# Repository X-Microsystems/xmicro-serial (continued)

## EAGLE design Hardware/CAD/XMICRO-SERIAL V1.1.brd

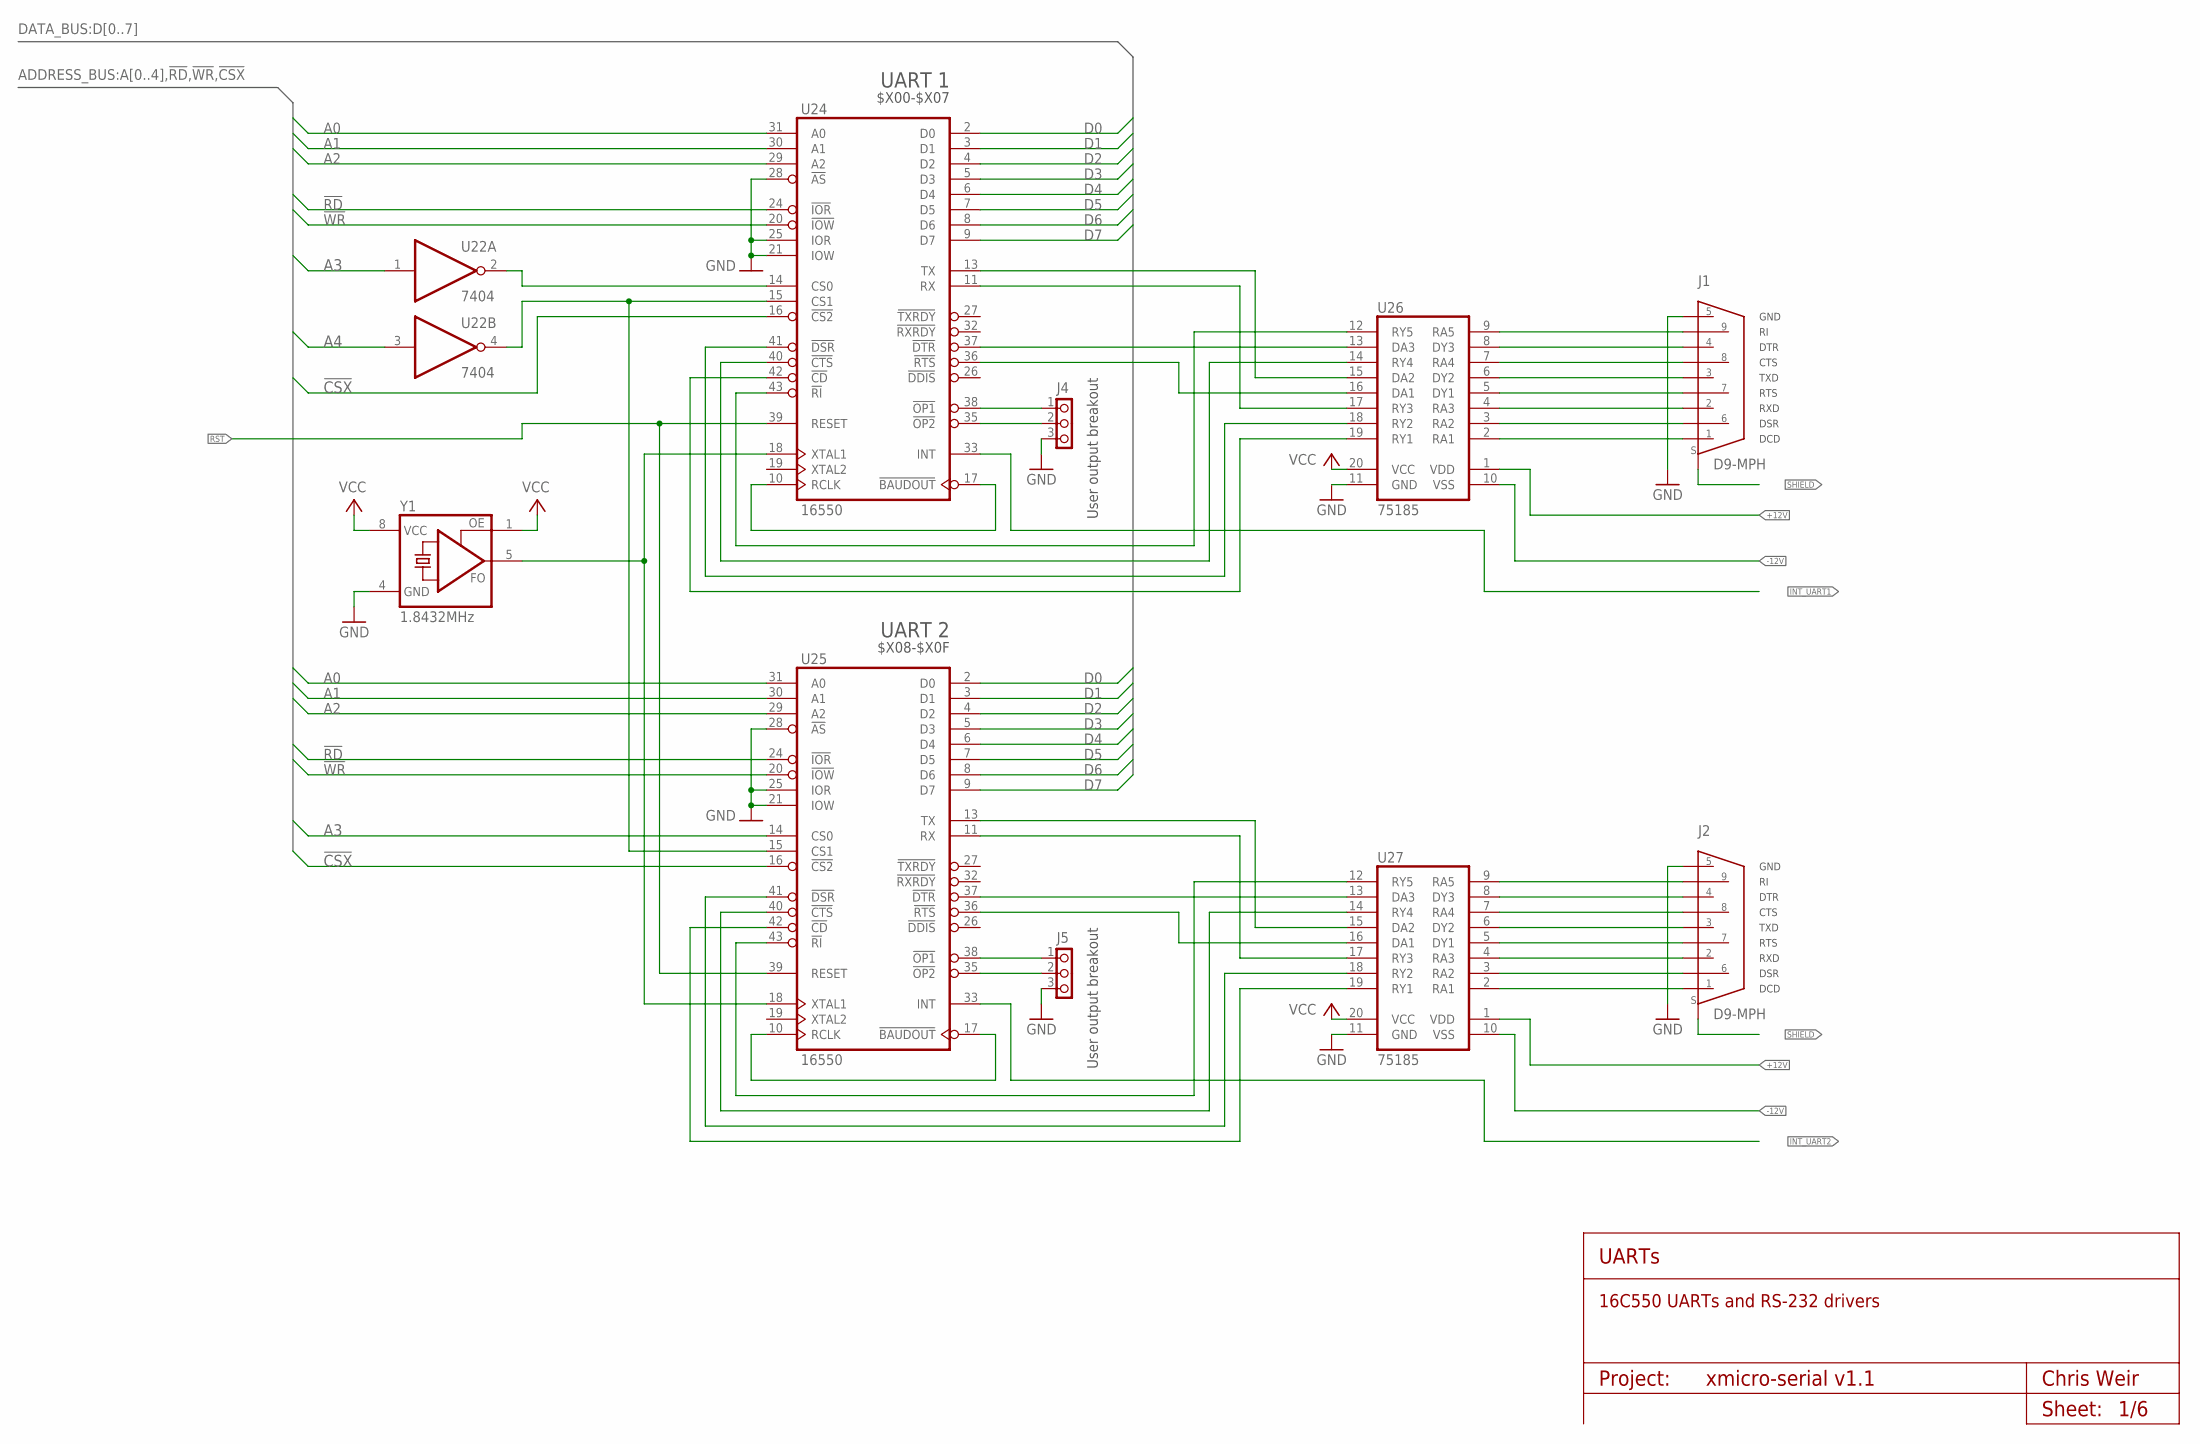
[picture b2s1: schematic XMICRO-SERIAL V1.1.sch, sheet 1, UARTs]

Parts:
J1, J2: D9-MPH; D9-H
J4, J5: PINHD1X3; 1X03
U22: 7404; DIL14
U24, U25: 16550; S44
U26, U27: 75185; DIL20
Y1: 1.8432MHz; DIL08S

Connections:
!CSX: U24.16 (!CS2), U25.16 (!CS2); also elsewhere on the board
!RD: U24.24 (!IOR), U25.24 (!IOR); also elsewhere on the board
!WR: U24.20 (!IOW), U25.20 (!IOW); also elsewhere on the board
+12V: U26.1 (VDD), U27.1 (VDD); also elsewhere on the board
-12V: U26.10 (VSS), U27.10 (VSS); also elsewhere on the board
A0: U24.31 (A0), U25.31 (A0); also elsewhere on the board
A1: U24.30 (A1), U25.30 (A1); also elsewhere on the board
A2: U24.29 (A2), U25.29 (A2); also elsewhere on the board
A3: U22.1 (I), U25.14 (CS0); also elsewhere on the board
A4: U22.3 (I); also elsewhere on the board
D0: U24.2 (D0), U25.2 (D0); also elsewhere on the board
D1: U24.3 (D1), U25.3 (D1); also elsewhere on the board
D2: U24.4 (D2), U25.4 (D2); also elsewhere on the board
D3: U24.5 (D3), U25.5 (D3); also elsewhere on the board
D4: U24.6 (D4), U25.6 (D4); also elsewhere on the board
D5: U24.7 (D5), U25.7 (D5); also elsewhere on the board
D6: U24.8 (D6), U25.8 (D6); also elsewhere on the board
D7: U24.9 (D7), U25.9 (D7); also elsewhere on the board
GND: J1.P$5, J2.P$5, J4.3, J5.3, U22.7 (GND), U24.21 (IOW), U24.22 (GND), U24.25 (IOR), U24.28 (!AS), U25.21 (IOW), U25.22 (GND), U25.25 (IOR), U25.28 (!AS), U26.11 (GND), U27.11 (GND), Y1.4 (GND); also elsewhere on the board
INT_UART1: U24.33 (INT); also elsewhere on the board
INT_UART2: U25.33 (INT); also elsewhere on the board
unnamed: J1.P$1, U26.2 (RA1)
unnamed: J1.P$2, U26.4 (RA3)
unnamed: J1.P$3, U26.6 (DY2)
unnamed: J1.P$4, U26.8 (DY3)
unnamed: J1.P$6, U26.3 (RA2)
unnamed: J1.P$7, U26.5 (DY1)
unnamed: J1.P$8, U26.7 (RA4)
unnamed: J1.P$9, U26.9 (RA5)
unnamed: J2.P$1, U27.2 (RA1)
unnamed: U24.43 (!RI), U26.12 (RY5)
unnamed: U24.37 (!DTR), U26.13 (DA3)
unnamed: U24.40 (!CTS), U26.14 (RY4)
unnamed: U24.13 (TX), U26.15 (DA2)
unnamed: U24.36 (!RTS), U26.16 (DA1)
unnamed: U24.11 (RX), U26.17 (RY3)
unnamed: U24.41 (!DSR), U26.18 (RY2)
unnamed: U24.42 (!CD), U26.19 (RY1)
unnamed: U24.10 (RCLK), U24.17 (!BAUDOUT)
unnamed: J2.P$2, U27.4 (RA3)
unnamed: J2.P$3, U27.6 (DY2)
unnamed: J2.P$4, U27.8 (DY3)
unnamed: J2.P$6, U27.3 (RA2)
unnamed: J2.P$7, U27.5 (DY1)
unnamed: J2.P$8, U27.7 (RA4)
unnamed: J2.P$9, U27.9 (RA5)
unnamed: U25.43 (!RI), U27.12 (RY5)
unnamed: U25.37 (!DTR), U27.13 (DA3)
unnamed: U25.40 (!CTS), U27.14 (RY4)
unnamed: U25.13 (TX), U27.15 (DA2)
unnamed: U25.36 (!RTS), U27.16 (DA1)
unnamed: U25.11 (RX), U27.17 (RY3)
unnamed: U25.41 (!DSR), U27.18 (RY2)
unnamed: U25.42 (!CD), U27.19 (RY1)
unnamed: U25.10 (RCLK), U25.17 (!BAUDOUT)
unnamed: U22.2 (O), U24.14 (CS0)
unnamed: U22.4 (O), U24.15 (CS1), U25.15 (CS1)
unnamed: U24.18 (XTAL1), U25.18 (XTAL1), Y1.5 (FO)
unnamed: J5.1, U25.38 (!OP1)
unnamed: J5.2, U25.35 (!OP2)
unnamed: J4.1, U24.38 (!OP1)
unnamed: J4.2, U24.35 (!OP2)
RST: U24.39 (RESET), U25.39 (RESET); also elsewhere on the board
SHIELD: J1.S1, J1.S2, J2.S1, J2.S2; also elsewhere on the board
VCC: U22.14 (VCC), U24.44 (VCC), U25.44 (VCC), U26.20 (VCC), U27.20 (VCC), Y1.1 (OE), Y1.8 (VCC); also elsewhere on the board

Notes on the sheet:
DTR
CTS
TXD
RTS
RXD
DSR
DCD
User output breakout
GND
Project:
UARTs
Chris Weir
Sheet:
16C550 UARTs and RS-232 drivers
UART 1
$X00-$X07
UART 2
$X08-$X0F

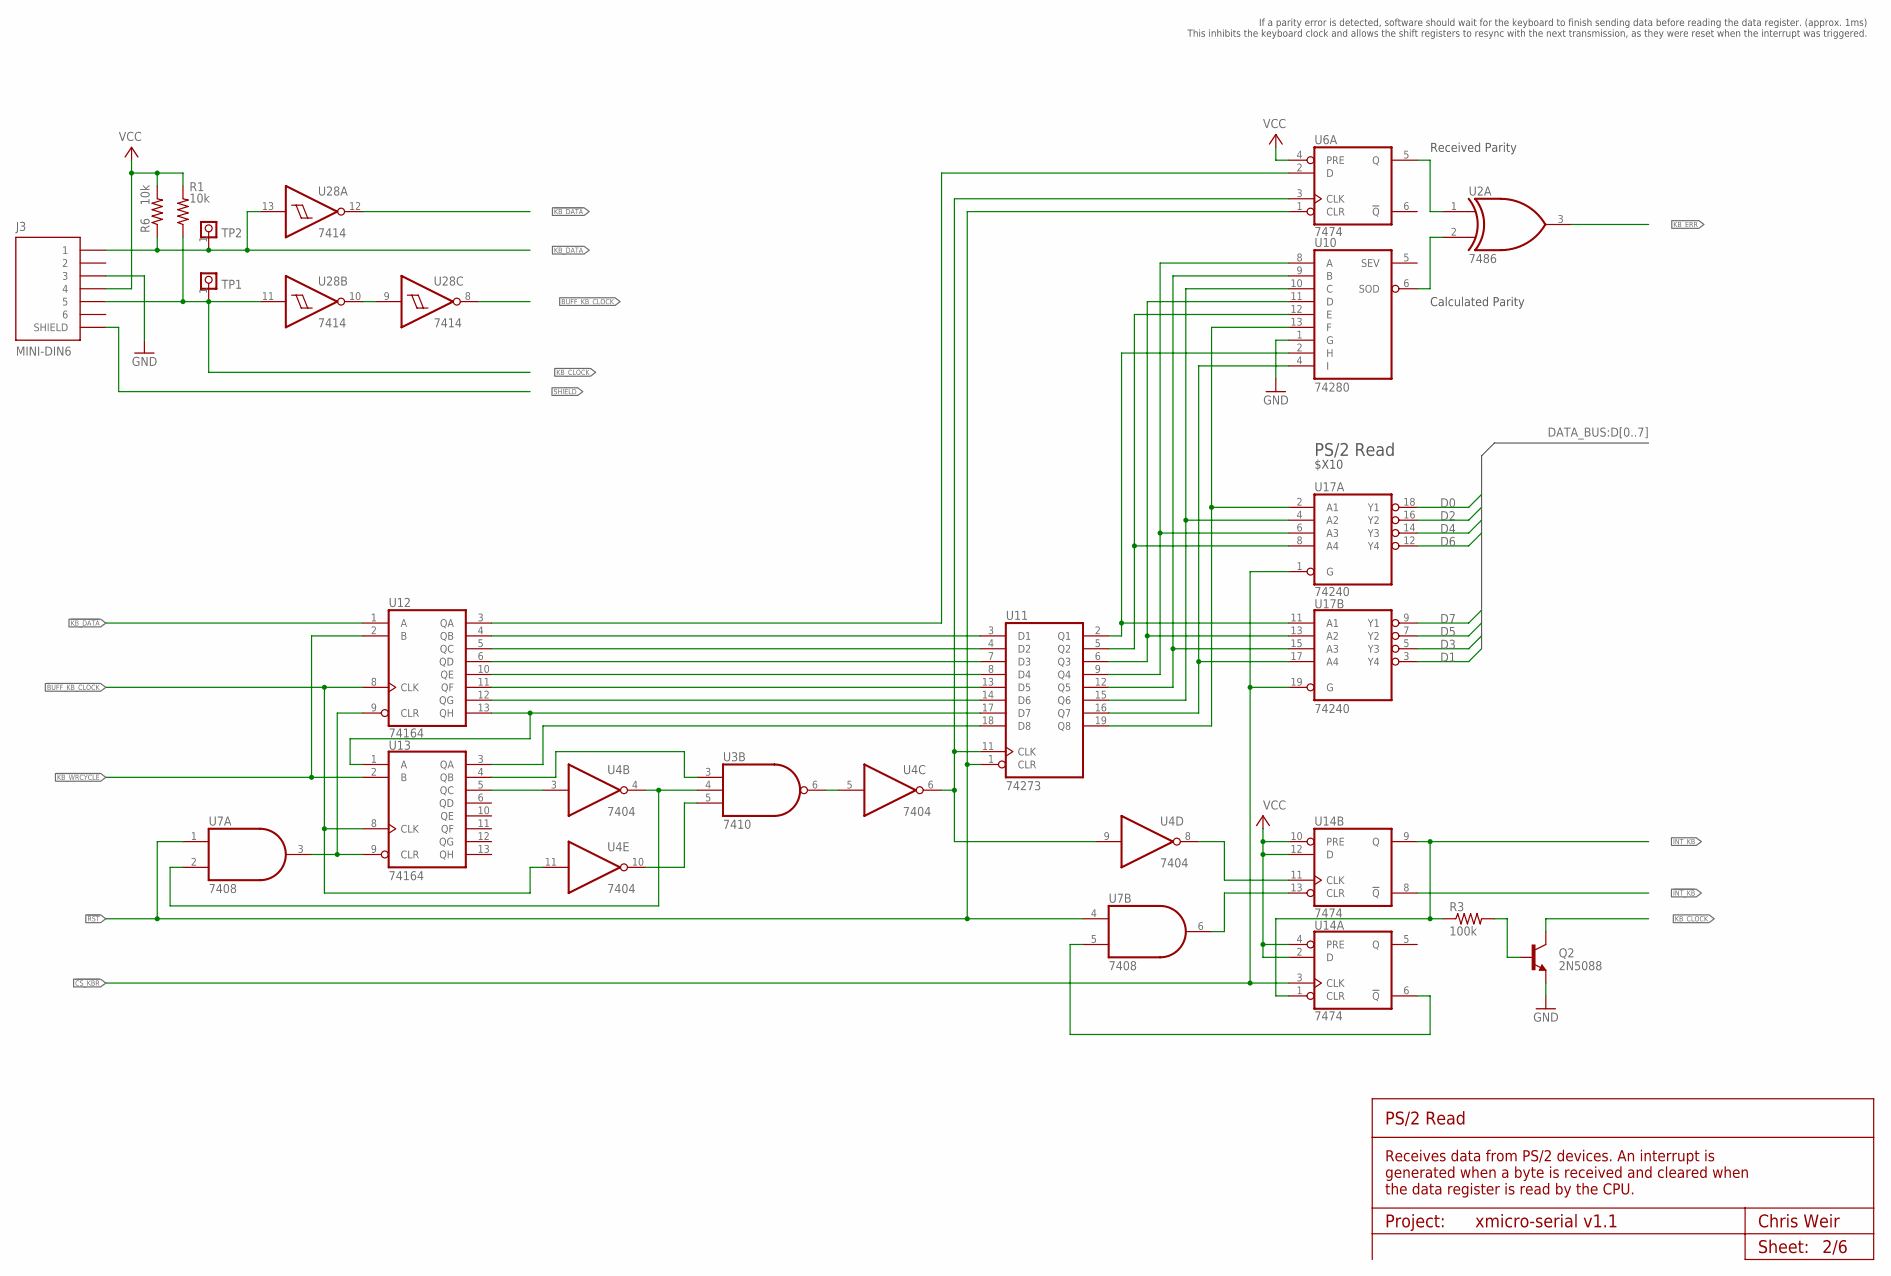
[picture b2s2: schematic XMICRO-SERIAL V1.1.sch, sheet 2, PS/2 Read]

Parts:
J3: MINI-DIN6
Q2: 2N5088; TO92
R1, R6: 10k; 0207/10
R3: 100k; 0207/10
TP1, TP2: PINHD-1X1; 1X01
U2: 7486; DIL14
U3: 7410; DIL14
U4: 7404; DIL14
U6, U14: 7474; DIL14
U7: 7408; DIL14
U10: 74280; DIL14
U11: 74273; DIL20
U12, U13: 74164; DIL14
U17: 74240; DIL20
U28: 7414; DIL14

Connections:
!CS_KBR: U14.3 (CLK), U17.1 (G), U17.19 (G); also elsewhere on the board
!INT_KB: U14.8 (!Q); also elsewhere on the board
!KB_DATA: U12.1 (A), U28.12 (O); also elsewhere on the board
!KB_WRCYCLE: U12.2 (B), U13.2 (B); also elsewhere on the board
!RST: U6.1 (CLR), U7.1 (I0), U7.4 (I0), U11.1 (CLR); also elsewhere on the board
BUFF_KB_CLOCK: U4.11 (I), U12.8 (CLK), U13.8 (CLK), U28.8 (O); also elsewhere on the board
D0: U17.18 (Y1); also elsewhere on the board
D1: U17.3 (Y4); also elsewhere on the board
D2: U17.16 (Y2); also elsewhere on the board
D3: U17.5 (Y3); also elsewhere on the board
D4: U17.14 (Y3); also elsewhere on the board
D5: U17.7 (Y2); also elsewhere on the board
D6: U17.12 (Y4); also elsewhere on the board
D7: U17.9 (Y1); also elsewhere on the board
GND: J3.3, Q2.1 (E), U2.7 (GND), U3.7 (GND), U4.7 (GND), U6.7 (GND), U7.7 (GND), U10.1 (G), U10.7 (GND), U11.10 (GND), U12.7 (GND), U13.7 (GND), U14.7 (GND), U17.10 (GND), U28.7 (GND); also elsewhere on the board
INT_KB: R3.1, U14.1 (CLR), U14.9 (Q); also elsewhere on the board
KB_CLOCK: J3.5, Q2.3 (C), R1.1, TP1.1, U28.11 (I); also elsewhere on the board
KB_DATA: J3.1, R6.1, TP2.1, U28.13 (I); also elsewhere on the board
KB_ERR: U2.3 (O); also elsewhere on the board
unnamed: U3.6 (O), U4.5 (I)
unnamed: U4.8 (O), U14.11 (CLK)
unnamed: U28.9 (I), U28.10 (O)
unnamed: U11.17 (D7), U12.13 (QH), U13.1 (A)
unnamed: U11.18 (D8), U13.3 (QA)
unnamed: U4.3 (I), U13.5 (QC)
unnamed: U3.4 (I1), U4.4 (O), U7.2 (I1)
unnamed: U4.6 (O), U4.9 (I), U6.3 (CLK), U11.11 (CLK)
unnamed: U3.3 (I0), U13.4 (QB)
unnamed: U11.14 (D6), U12.12 (QG)
unnamed: U11.13 (D5), U12.11 (QF)
unnamed: U11.7 (D3), U12.6 (QD)
unnamed: U11.4 (D2), U12.5 (QC)
unnamed: U11.3 (D1), U12.4 (QB)
unnamed: U6.2 (D), U12.3 (QA)
unnamed: U7.3 (O), U12.9 (CLR), U13.9 (CLR)
unnamed: U7.6 (O), U14.13 (CLR)
unnamed: U2.1 (I0), U6.5 (Q)
unnamed: U10.13 (F), U11.19 (Q8), U17.2 (A1)
unnamed: U10.4 (I), U11.16 (Q7), U17.17 (A4)
unnamed: U10.10 (C), U11.15 (Q6), U17.4 (A2)
unnamed: U10.9 (B), U11.12 (Q5), U17.15 (A3)
unnamed: U10.11 (D), U11.6 (Q3), U17.13 (A2)
unnamed: U10.12 (E), U11.5 (Q2), U17.8 (A4)
unnamed: U10.2 (H), U11.2 (Q1), U17.11 (A1)
unnamed: U10.8 (A), U11.9 (Q4), U17.6 (A3)
unnamed: U2.2 (I1), U10.6 (SOD)
unnamed: U3.5 (I2), U4.10 (O)
unnamed: Q2.2 (B), R3.2
unnamed: U7.5 (I1), U14.6 (!Q)
SHIELD: J3.G$1 (SHIELD), J3.G$2 (SHIELD), J3.G$3 (SHIELD); also elsewhere on the board
UC4: U11.8 (D4), U12.10 (QE)
VCC: J3.4, R1.2, R6.2, U2.14 (VCC), U3.14 (VCC), U4.14 (VCC), U6.4 (PRE), U6.14 (VCC), U7.14 (VCC), U10.14 (VCC), U11.20 (VCC), U12.14 (VCC), U13.14 (VCC), U14.2 (D), U14.4 (PRE), U14.10 (PRE), U14.12 (D), U14.14 (VCC), U17.20 (VCC), U28.14 (VCC); also elsewhere on the board

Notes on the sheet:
Received Parity
Calculated Parity
If a parity error is detected, software should wait for the keyboard to finish sending data before reading the data register. (approx. 1ms) This inhibits the keyboard clock and allows the shift registers to resync with the next transmission, as they were reset when the interrupt was triggered.
Project:
PS/2 Read
Chris Weir
Sheet:
Receives data from PS/2 devices. An interrupt is generated when a byte is received and cleared when the data register is read by the CPU.
$X10

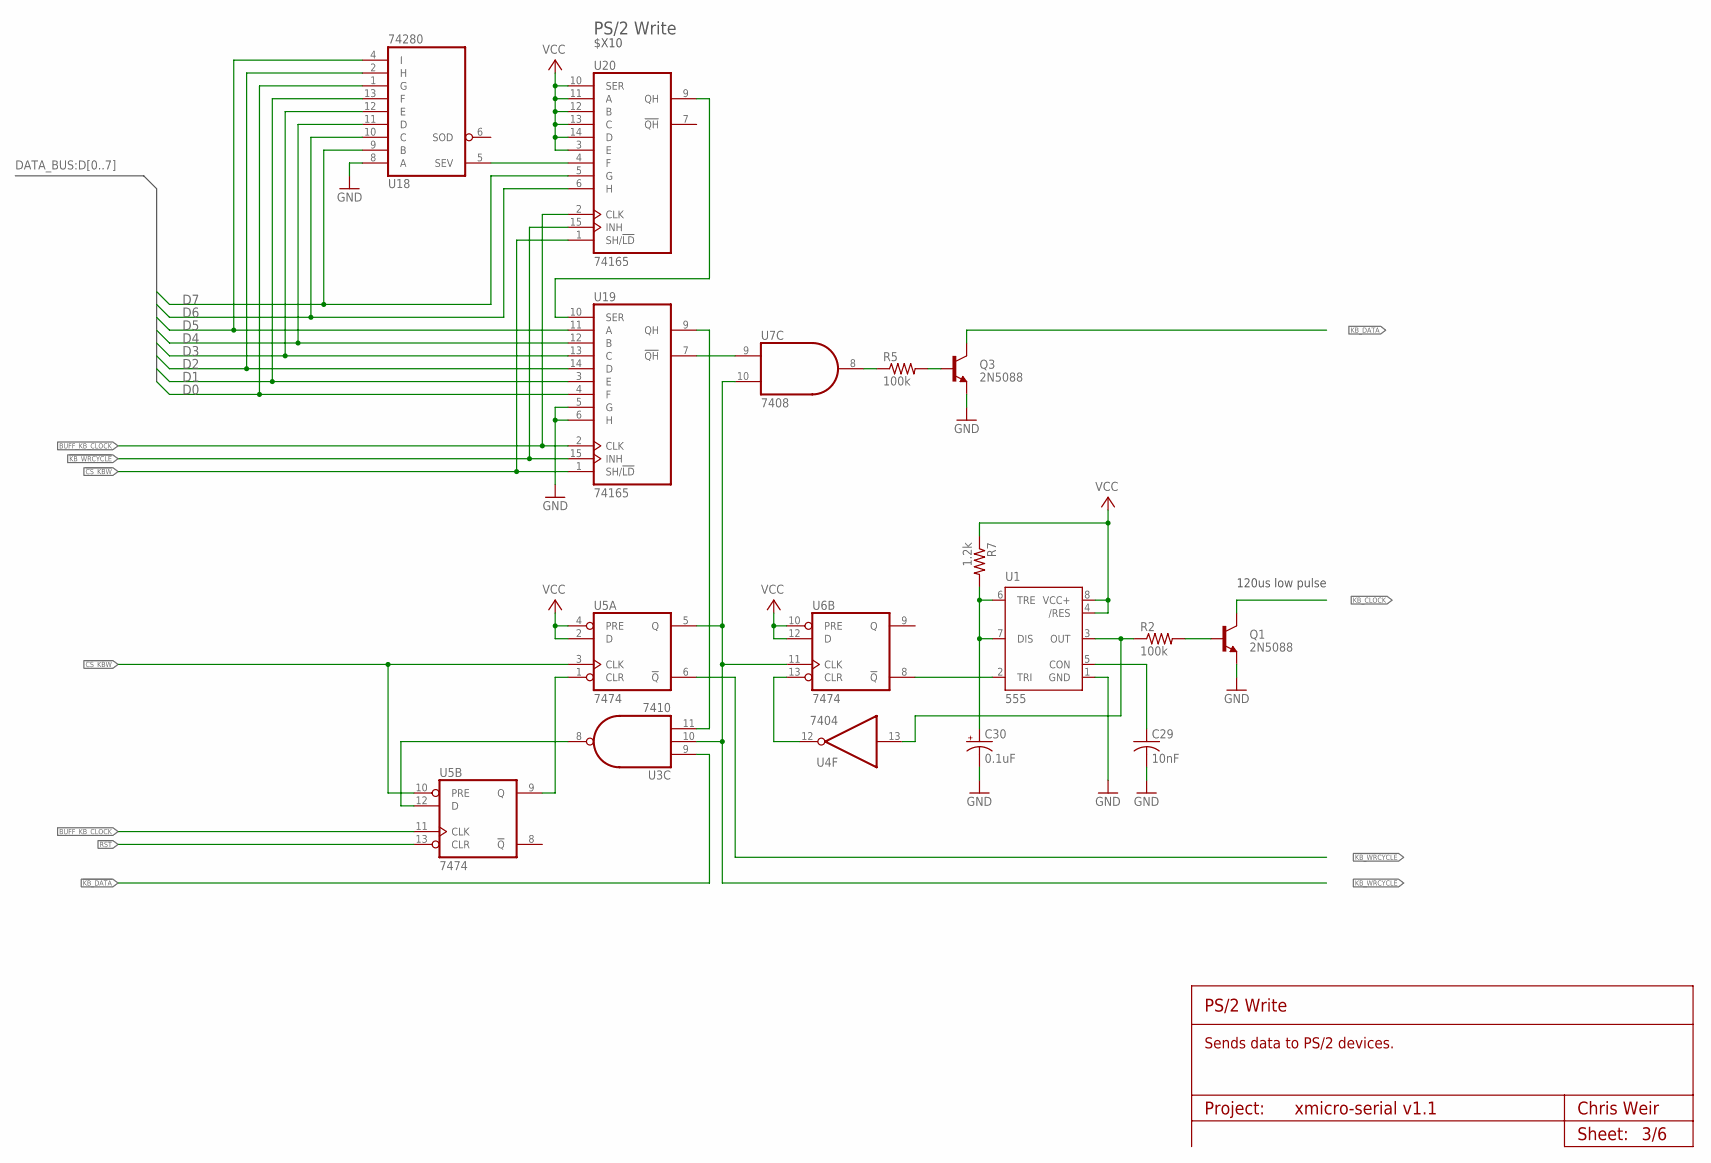
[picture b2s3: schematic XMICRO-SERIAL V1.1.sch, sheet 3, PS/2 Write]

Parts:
C29: 10nF; C100
C30: 0.1uF; E2,5-6
Q1, Q3: 2N5088; TO92
R2, R5: 100k; 0207/10
R7: 1.2k; 0207/10
U1: 555; DIL-08
U3: 7410; DIL14
U4: 7404; DIL14
U5, U6: 7474; DIL14
U7: 7408; DIL14
U18: 74280; DIL14
U19, U20: 74165; DIL16

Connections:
!CS_KBW: U5.3 (CLK), U5.10 (PRE), U19.1 (SH/!LD), U20.1 (SH/!LD); also elsewhere on the board
!KB_DATA: U3.9 (I0); also elsewhere on the board
!KB_WRCYCLE: U5.6 (!Q), U19.15 (INH), U20.15 (INH); also elsewhere on the board
!RST: U5.13 (CLR); also elsewhere on the board
BUFF_KB_CLOCK: U5.11 (CLK), U19.2 (CLK), U20.2 (CLK); also elsewhere on the board
D0: U18.1 (G), U19.4 (F); also elsewhere on the board
D1: U18.13 (F), U19.3 (E); also elsewhere on the board
D2: U18.2 (H), U19.14 (D); also elsewhere on the board
D3: U18.12 (E), U19.13 (C); also elsewhere on the board
D4: U18.11 (D), U19.12 (B); also elsewhere on the board
D5: U18.4 (I), U19.11 (A); also elsewhere on the board
D6: U18.10 (C), U20.6 (H); also elsewhere on the board
D7: U18.9 (B), U20.5 (G); also elsewhere on the board
GND: C29.P$2 (2), C30.-, Q1.1 (E), Q3.1 (E), U1.1 (GND), U3.7 (GND), U4.7 (GND), U5.7 (GND), U6.7 (GND), U7.7 (GND), U18.7 (GND), U18.8 (A), U19.5 (G), U19.6 (H), U19.8 (GND), U20.8 (GND); also elsewhere on the board
KB_CLOCK: Q1.3 (C); also elsewhere on the board
KB_DATA: Q3.3 (C); also elsewhere on the board
KB_WRCYCLE: U3.10 (I1), U5.5 (Q), U6.11 (CLK), U7.10 (I1); also elsewhere on the board
unnamed: U3.8 (O), U5.12 (D)
unnamed: U4.12 (O), U6.13 (CLR)
unnamed: U3.11 (I2), U19.9 (QH)
unnamed: U7.9 (I0), U19.7 (!QH)
unnamed: R5.1, U7.8 (O)
unnamed: U19.10 (SER), U20.9 (QH)
unnamed: U18.5 (SEV), U20.4 (F)
unnamed: Q3.2 (B), R5.2
unnamed: Q1.2 (B), R2.2
unnamed: U5.1 (CLR), U5.9 (Q)
unnamed: U1.2 (TRI), U6.8 (!Q)
unnamed: C30.+, R7.2, U1.6 (TRE), U1.7 (DIS)
unnamed: R2.1, U1.3 (OUT), U4.13 (I)
unnamed: C29.P$1 (1), U1.5 (CON)
VCC: R7.1, U1.4 (/RES), U1.8 (VCC+), U3.14 (VCC), U4.14 (VCC), U5.2 (D), U5.4 (PRE), U5.14 (VCC), U6.10 (PRE), U6.12 (D), U6.14 (VCC), U7.14 (VCC), U18.14 (VCC), U19.16 (VCC), U20.3 (E), U20.10 (SER), U20.11 (A), U20.12 (B), U20.13 (C), U20.14 (D), U20.16 (VCC); also elsewhere on the board

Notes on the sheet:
120us low pulse
Project:
PS/2 Write
Chris Weir
Sheet:
Sends data to PS/2 devices.
$X10

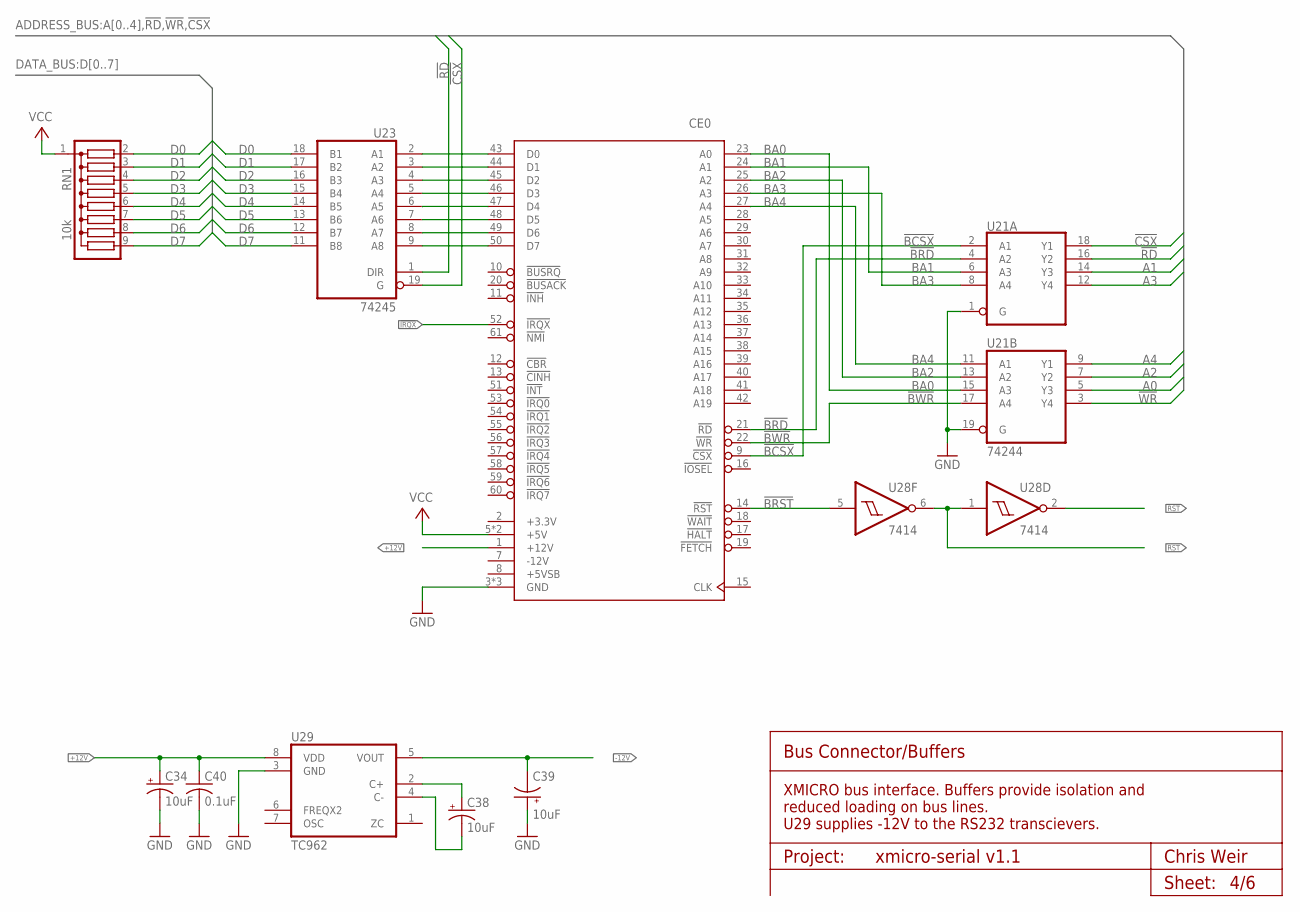
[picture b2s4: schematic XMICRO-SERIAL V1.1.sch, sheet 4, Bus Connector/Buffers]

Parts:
C34, C38, C39: 10uF; E2,5-5
C40: 0.1uF; C100
CE0: XMICRO-BUS-EDGE62M; EDGE62M
RN1: 10k; SIL9
U21: 74244; DIL20
U23: 74245; DIL20
U28: 7414; DIL14
U29: TC962; DIL8

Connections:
!BCSX: CE0.9 (!CSX), U21.2 (A1)
!BRD: CE0.21 (!RD), U21.4 (A2)
!BRST: CE0.14 (!RST), U28.5 (I)
!BWR: CE0.22 (!WR), U21.17 (A4)
!CSX: U21.18 (Y1), U23.19 (G); also elsewhere on the board
!IRQX: CE0.52 (!IRQX); also elsewhere on the board
!RD: U21.16 (Y2), U23.1 (DIR); also elsewhere on the board
!RST: U28.2 (O); also elsewhere on the board
!WR: U21.3 (Y4); also elsewhere on the board
+12V: C34.+, C40.P$1 (1), CE0.1 (+12V), U29.8 (VDD); also elsewhere on the board
-12V: C39.-, U29.5 (VOUT); also elsewhere on the board
A0: U21.5 (Y3); also elsewhere on the board
A1: U21.14 (Y3); also elsewhere on the board
A2: U21.7 (Y2); also elsewhere on the board
A3: U21.12 (Y4); also elsewhere on the board
A4: U21.9 (Y1); also elsewhere on the board
BA0: CE0.23 (A0), U21.15 (A3)
BA1: CE0.24 (A1), U21.6 (A3)
BA2: CE0.25 (A2), U21.13 (A2)
BA3: CE0.26 (A3), U21.8 (A4)
BA4: CE0.27 (A4), U21.11 (A1)
D0: RN1.2, U23.18 (B1); also elsewhere on the board
D1: RN1.3, U23.17 (B2); also elsewhere on the board
D2: RN1.4, U23.16 (B3); also elsewhere on the board
D3: RN1.5, U23.15 (B4); also elsewhere on the board
D4: RN1.6, U23.14 (B5); also elsewhere on the board
D5: RN1.7, U23.13 (B6); also elsewhere on the board
D6: RN1.8, U23.12 (B7); also elsewhere on the board
D7: RN1.9, U23.11 (B8); also elsewhere on the board
GND: C34.-, C39.+, C40.P$2 (2), CE0.3 (GND), CE0.4 (GND), CE0.62 (GND), U21.1 (G), U21.10 (GND), U21.19 (G), U23.10 (GND), U28.7 (GND), U29.3 (GND); also elsewhere on the board
unnamed: C38.-, U29.4 (C-)
unnamed: CE0.50 (D7), U23.9 (A8)
unnamed: CE0.49 (D6), U23.8 (A7)
unnamed: CE0.48 (D5), U23.7 (A6)
unnamed: CE0.47 (D4), U23.6 (A5)
unnamed: CE0.46 (D3), U23.5 (A4)
unnamed: CE0.45 (D2), U23.4 (A3)
unnamed: CE0.44 (D1), U23.3 (A2)
unnamed: CE0.43 (D0), U23.2 (A1)
unnamed: C38.+, U29.2 (C+)
RST: U28.1 (I), U28.6 (O); also elsewhere on the board
VCC: CE0.5 (+5V), CE0.6 (+5V), RN1.1, U21.20 (VCC), U23.20 (VCC), U28.14 (VCC); also elsewhere on the board

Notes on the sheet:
Project:
Bus Connector/Buffers
Chris Weir
Sheet:
XMICRO bus interface. Buffers provide isolation and reduced loading on bus lines. U29 supplies -12V to the RS232 transcievers.

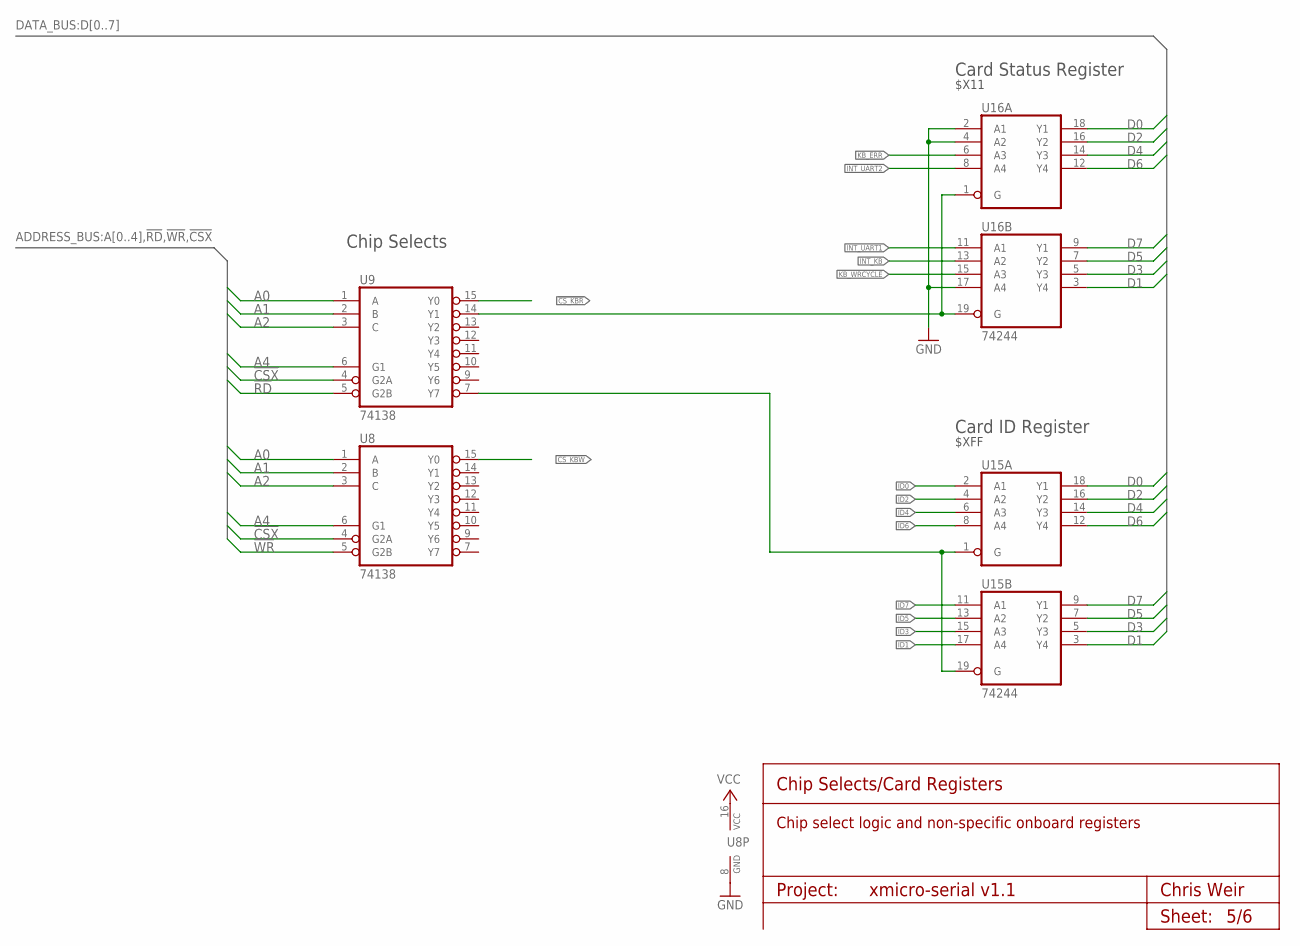
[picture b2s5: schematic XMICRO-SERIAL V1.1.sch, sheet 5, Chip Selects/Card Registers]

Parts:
U8, U9: 74138; DIL16
U15, U16: 74244; DIL20

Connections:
!CSX: U8.4 (G2A), U9.4 (G2A); also elsewhere on the board
!CS_IDR: U9.7 (Y7), U15.1 (G), U15.19 (G)
!CS_KBR: U9.15 (Y0); also elsewhere on the board
!CS_KBW: U8.15 (Y0); also elsewhere on the board
!CS_STR: U9.14 (Y1), U16.1 (G), U16.19 (G)
!RD: U9.5 (G2B); also elsewhere on the board
!WR: U8.5 (G2B); also elsewhere on the board
A0: U8.1 (A), U9.1 (A); also elsewhere on the board
A1: U8.2 (B), U9.2 (B); also elsewhere on the board
A2: U8.3 (C), U9.3 (C); also elsewhere on the board
A4: U8.6 (G1), U9.6 (G1); also elsewhere on the board
D0: U15.18 (Y1), U16.18 (Y1); also elsewhere on the board
D1: U15.3 (Y4), U16.3 (Y4); also elsewhere on the board
D2: U15.16 (Y2), U16.16 (Y2); also elsewhere on the board
D3: U15.5 (Y3), U16.5 (Y3); also elsewhere on the board
D4: U15.14 (Y3), U16.14 (Y3); also elsewhere on the board
D5: U15.7 (Y2), U16.7 (Y2); also elsewhere on the board
D6: U15.12 (Y4), U16.12 (Y4); also elsewhere on the board
D7: U15.9 (Y1), U16.9 (Y1); also elsewhere on the board
GND: U8.8 (GND), U9.8 (GND), U15.10 (GND), U16.2 (A1), U16.4 (A2), U16.10 (GND), U16.17 (A4); also elsewhere on the board
ID0: U15.2 (A1)
ID1: U15.17 (A4)
ID2: U15.4 (A2)
ID3: U15.15 (A3)
ID4: U15.6 (A3)
ID5: U15.13 (A2)
ID6: U15.8 (A4)
ID7: U15.11 (A1)
INT_KB: U16.13 (A2); also elsewhere on the board
INT_UART1: U16.11 (A1); also elsewhere on the board
INT_UART2: U16.8 (A4); also elsewhere on the board
KB_ERR: U16.6 (A3); also elsewhere on the board
KB_WRCYCLE: U16.15 (A3); also elsewhere on the board
VCC: U8.16 (VCC), U9.16 (VCC), U15.20 (VCC), U16.20 (VCC); also elsewhere on the board

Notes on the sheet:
Card ID Register
$XFF
Chip Selects
Project:
Chip Selects/Card Registers
Chris Weir
Sheet:
Chip select logic and non-specific onboard registers
Card Status Register
$X11

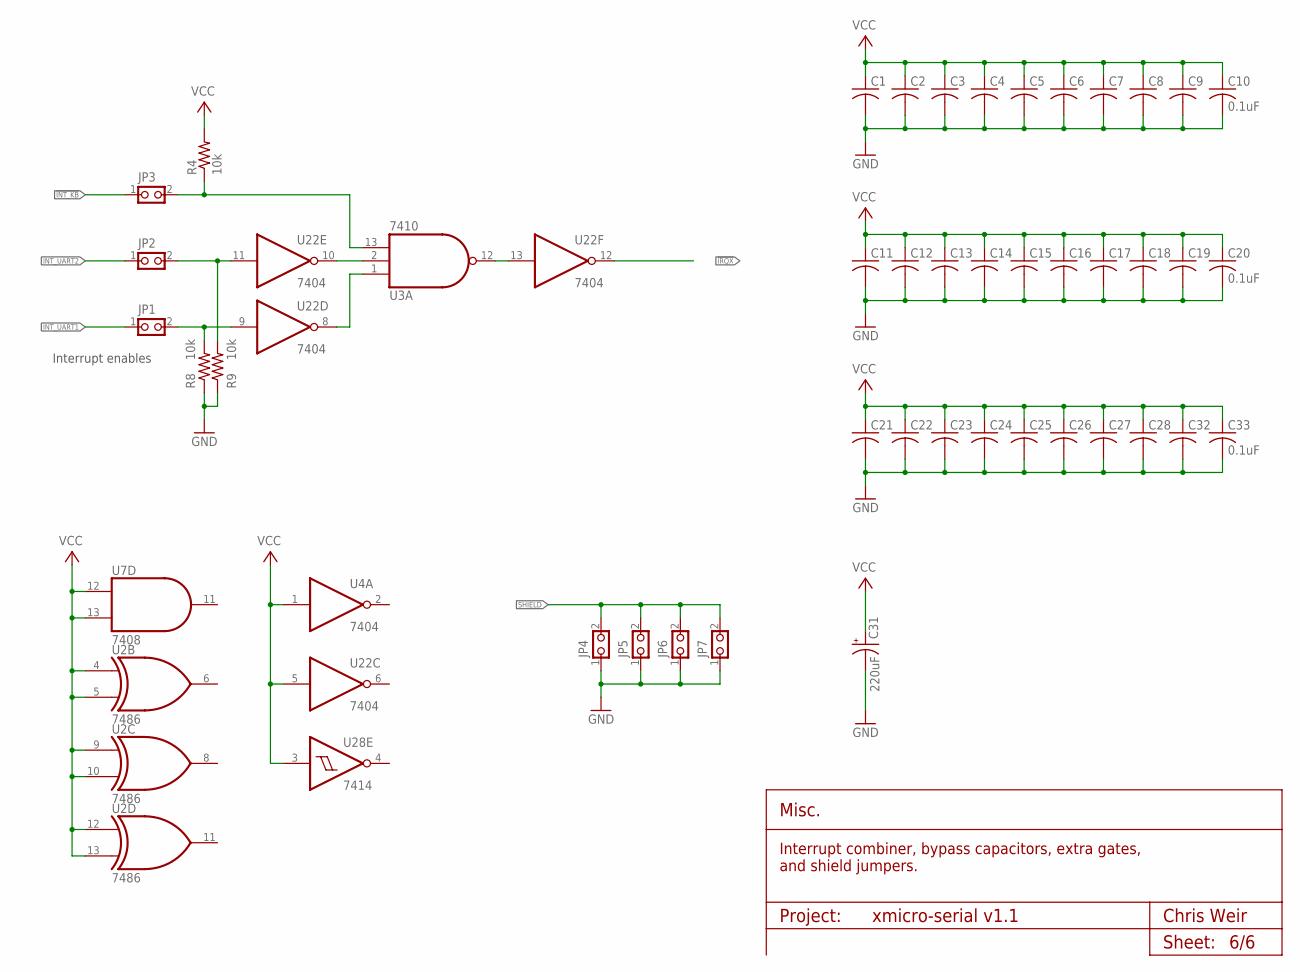
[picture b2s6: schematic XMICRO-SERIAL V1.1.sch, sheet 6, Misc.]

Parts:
C1, C2, C3, C4, C5, C6, C7, C8, C9, C10, C11, C12, C13, C14, C15, C16, C17, C18, C19, C20, C21, C22, C23, C24, C25, C26, C27, C28, C32, C33: 0.1uF; C100
C31: 220uF; C-10-5
JP1, JP2, JP3, JP4, JP5, JP6, JP7: PINHD-1X2THRU; 1X02
R4, R8, R9: 10k; 0207/10
U2: 7486; DIL14
U3: 7410; DIL14
U4, U22: 7404; DIL14
U7: 7408; DIL14
U28: 7414; DIL14

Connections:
!INT_KB: JP3.1; also elsewhere on the board
!IRQX: U22.12 (O); also elsewhere on the board
GND: C1.P$2 (2), C2.P$2 (2), C3.P$2 (2), C4.P$2 (2), C5.P$2 (2), C6.P$2 (2), C7.P$2 (2), C8.P$2 (2), C9.P$2 (2), C10.P$2 (2), C11.P$2 (2), C12.P$2 (2), C13.P$2 (2), C14.P$2 (2), C15.P$2 (2), C16.P$2 (2), C17.P$2 (2), C18.P$2 (2), C19.P$2 (2), C20.P$2 (2), C21.P$2 (2), C22.P$2 (2), C23.P$2 (2), C24.P$2 (2), C25.P$2 (2), C26.P$2 (2), C27.P$2 (2), C28.P$2 (2), C31.-, C32.P$2 (2), C33.P$2 (2), JP4.1, JP5.1, JP6.1, JP7.1, R8.1, R9.1, U2.7 (GND), U3.7 (GND), U4.7 (GND), U7.7 (GND), U22.7 (GND), U28.7 (GND); also elsewhere on the board
INT_UART1: JP1.1; also elsewhere on the board
INT_UART2: JP2.1; also elsewhere on the board
unnamed: U3.12 (O), U22.13 (I)
unnamed: JP3.2, R4.1, U3.13 (I2)
unnamed: U3.1 (I0), U22.8 (O)
unnamed: U3.2 (I1), U22.10 (O)
unnamed: JP1.2, R8.2, U22.9 (I)
unnamed: JP2.2, R9.2, U22.11 (I)
SHIELD: JP4.2, JP5.2, JP6.2, JP7.2; also elsewhere on the board
VCC: C1.P$1 (1), C2.P$1 (1), C3.P$1 (1), C4.P$1 (1), C5.P$1 (1), C6.P$1 (1), C7.P$1 (1), C8.P$1 (1), C9.P$1 (1), C10.P$1 (1), C11.P$1 (1), C12.P$1 (1), C13.P$1 (1), C14.P$1 (1), C15.P$1 (1), C16.P$1 (1), C17.P$1 (1), C18.P$1 (1), C19.P$1 (1), C20.P$1 (1), C21.P$1 (1), C22.P$1 (1), C23.P$1 (1), C24.P$1 (1), C25.P$1 (1), C26.P$1 (1), C27.P$1 (1), C28.P$1 (1), C31.+, C32.P$1 (1), C33.P$1 (1), R4.2, U2.4 (I0), U2.5 (I1), U2.9 (I0), U2.10 (I1), U2.12 (I0), U2.13 (I1), U2.14 (VCC), U3.14 (VCC), U4.1 (I), U4.14 (VCC), U7.12 (I0), U7.13 (I1), U7.14 (VCC), U22.5 (I), U22.14 (VCC), U28.3 (I), U28.14 (VCC); also elsewhere on the board

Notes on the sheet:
Interrupt enables
Project:
Misc.
Chris Weir
Sheet:
Interrupt combiner, bypass capacitors, extra gates, and shield jumpers.

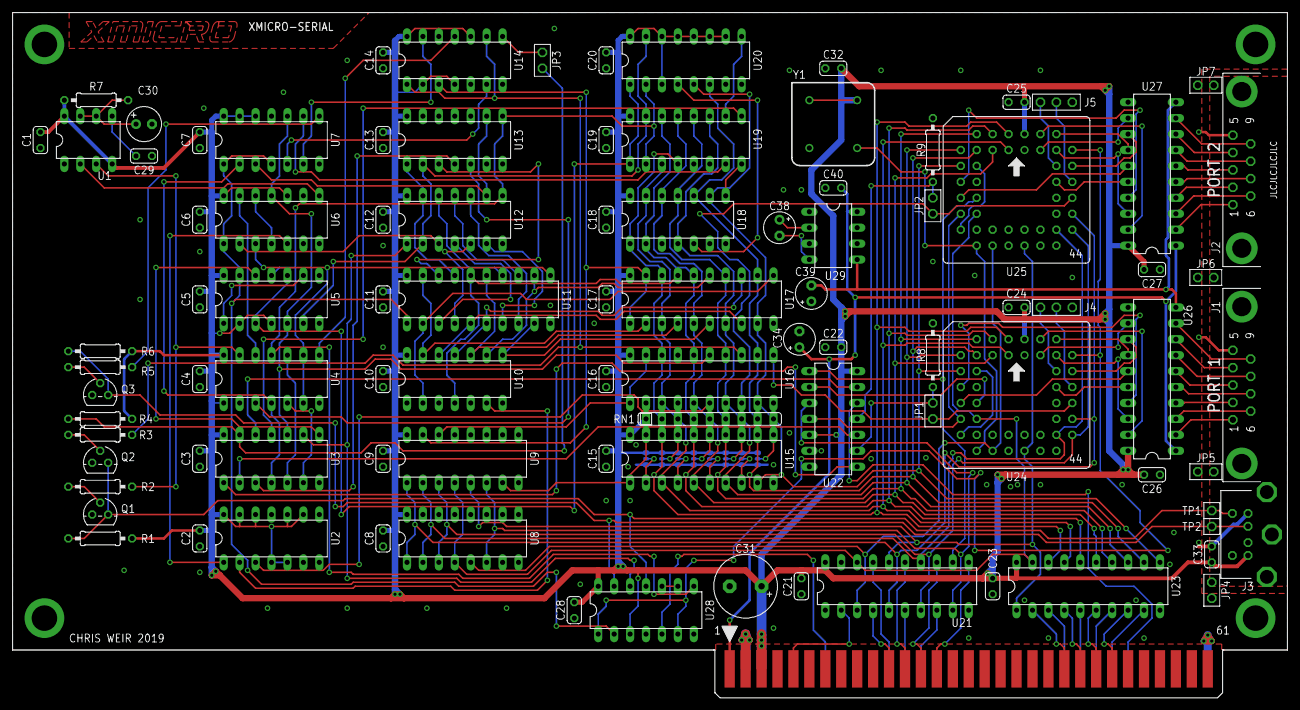
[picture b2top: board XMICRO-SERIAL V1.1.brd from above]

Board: 2 copper layers, 203.2 x 109.2 mm, 95 parts (0 on the bottom side), 150 nets.

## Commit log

2019-03-23 Reogranized directory structure
2019-03-23 Completed the technical manual
2019-05-28 Updated schematic xrefs to indicate signal direction.
2019-10-27 Updated design to V1.1 - added Schmitt trigger inputs, improved connector spacing, fixed PS/2 connector footprint
2019-10-27 Fixed a schematic issue - added second inverter to BUFF_KB_CLOCK signal.
2019-11-20 Updated to hardware V1.1.
2020-08-29 Added picture and updated README.md
2024-09-09 Initial commit for finalized V1.0
2024-09-15 Rearranged files
2024-09-29 Updated datasheet formatting
2024-09-30 Updated datasheet template
2025-08-05 Updated Readme and photos
